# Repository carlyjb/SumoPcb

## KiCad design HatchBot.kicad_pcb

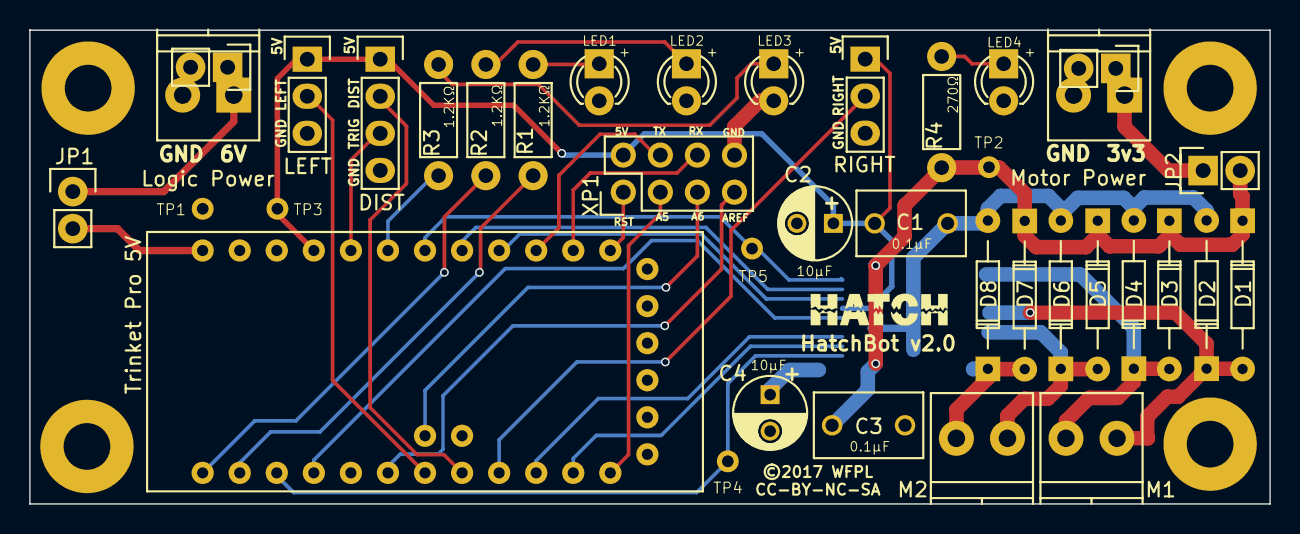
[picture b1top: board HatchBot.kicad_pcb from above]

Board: 2 copper layers, 85.0 x 32.5 mm, 37 parts (1 on the bottom side), 34 nets.

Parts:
C1, C3: 0.1µF; C_Disc_D7.5_P5
C2, C4: 10µF; C_Radial_D5_L6_P2.5
D1, D2, D3, D4, D5, D6, D7, D8: 1N4001; Diode_DO-35_SOD27_Horizontal_RM10
J1: Trinket Pro 5V; Trinket_Pro_5V
JP1: JP1; Pin_Header_Straight_1x02
JP2: JP2; Pin_Header_Straight_1x02
LED1, LED2, LED3, LED4: LED; LED-3MM
LPWR1: Logic Power; TerminalBlock_Pheonix_PT-3.5mm_2pol
M1: Motor1; TerminalBlock_Pheonix_PT-3.5mm_2pol
M2: Motor2; TerminalBlock_Pheonix_PT-3.5mm_2pol
Motor Power: Motor Power; TerminalBlock_Pheonix_PT-3.5mm_2pol
P1: DIST; Pin_Header_Straight_1x04
P2: LEFT; Pin_Header_Straight_1x03
P3: RIGHT; Pin_Header_Straight_1x03
R1, R2, R3: 1.2KΩ; Resistor_Horizontal_RM7mm
R4: 270Ω; Resistor_Horizontal_RM7mm
TP1: GND TEST; Measurement_Point_Round-TH_Small
TP2: V_MOTOR TEST; Measurement_Point_Round-TH_Small
TP3: V_LOGIC TEST; Measurement_Point_Round-TH_Small
TP4: PWMB TEST; Measurement_Point_Round-TH_Small
TP5: PWMA TEST; Measurement_Point_Round-TH_Small
U1: TB6612FNG; SSOP-24_5.3x8.2mm_Pitch0.65mm
XP1: EXP; Pin_Header_Straight_2x04

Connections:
A01: D3.2, D4.1, M1.1, U1.1, U1.2
A02: D1.2, D2.1, M1.2, U1.5, U1.6
A5: J1.25, XP1.3
A6: J1.26, XP1.5
AIN1: J1.3, U1.21
AIN2: J1.4, U1.22
AREF: J1.19, XP1.7
B01: D7.2, D8.1, M2.1, U1.11, U1.12
B02: D5.2, D6.1, M2.2, U1.7, U1.8
BIN1: J1.23, U1.17
BIN2: J1.24, U1.16
GND_LOGIC: C1.2, C2.2, C3.2, C4.2, D2.2, D4.2, D6.2, D8.2, J1.16, LED1.1, LED2.1, LED3.1, LED4.1, LPWR1.2, Motor Power.2, P1.4, P2.3, P3.3, TP1.1, U1.3, U1.4, U1.9, U1.10, U1.18, XP1.8
LED1: J1.10, R1.1
LED2: J1.9, R2.1
LED3: J1.6, R3.1
unnamed: LED1.2, R1.2
unnamed: LED2.2, R2.2
unnamed: LED3.2, R3.2
unnamed: LED4.2, R4.2
PWMA: J1.5, TP5.1, U1.23
PWMB: J1.11, TP4.1, U1.15
RST: J1.1, XP1.1
RX: J1.34, XP1.6
SENS_DIST: J1.21, P1.2
SENS_LEFT: J1.20, P2.2
SENS_RIGHT: J1.22, P3.2
STBY: J1.12, U1.19
TRIG_DIST: J1.8, P1.3
TX: J1.35, XP1.4
V_BAT: J1.17, JP1.2
V_BAT_IN: JP1.1, LPWR1.1
V_LOGIC: C1.1, C2.1, J1.14, P1.1, P2.1, P3.1, TP3.1, U1.20, XP1.2
V_MOTOR: C3.1, C4.1, D1.1, D3.1, D5.1, D7.1, JP2.2, R4.1, TP2.1, U1.13, U1.14, U1.24
V_MOTOR_IN: JP2.1, Motor Power.1

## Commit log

2016-07-21 :circus_tent: Added .gitattributes & .gitignore files
2016-07-21 Added files
    Added files for sumo bot pcb board. Does not break out extra pins.
2016-07-22 First spin using bare SMT TB6612FNG.
2016-07-22 New spin!
2016-08-31 Sumo v1 files
2016-12-31 Ditch backup files and add to .gitignore
2016-12-31 Drop old V0 files — that’s the version before we split the motor and logic power into separate areas.
2016-12-31 Drop Gerber files and Adafruit Pro Trinket board files
2016-12-31 Rename MyArduinoLib to HatchLib
2017-01-12 Rename “Sumo 1” -> HatchBot.
2017-01-12 Rename ArduinoFootprints -> HatchFootprints
2017-01-12 Scrap kicad_tutorial directory
2017-02-27 Spin 2, first cut.
2017-02-28 Move the motor-power section a bit to the right. Flip the LEDs. Fix up some labels.
2017-03-02 Final tweaks (more sane test point placement, switch back to filled zones for doubled pads, add the Hatch logo).
2017-03-02 Gerber files.
2017-03-02 Include JPEG source for Hatch logo
2017-03-02 Docs.
2017-03-02 Note on LEDs.

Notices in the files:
HatchBot.kicad_pcb:
©2017 WFPL
CC-BY-NC-SA
